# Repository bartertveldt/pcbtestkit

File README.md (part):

# PCB TestKit

**From a KiCad board to a production-test kit in one click: weak-point analysis, the fab class to order, a test
plan, a pogo-pin test fixture PCB, a 3D-printed solder jig, a Raspberry Pi test runner and an animated explainer
video. Built so AI assistants can drive it cheaply.**

*Rendered by KiCad itself from the KiCad demo board pic_programmer: the 55 hand-soldered parts are fitted with
the PCB top side up in the generated placement jig, the holding jig closes over them, the stack is turned over,
the placement jig comes off and every lead is soldered.*

---

## Contents

- [What you get](#what-you-get)
- [Install](#install)
- [Quick start](#quick-start)
- [Using it in KiCad](#using-it-in-kicad)
- [Command line](#command-line)
- [Technology classes: which fab and class to order](#technology-classes-which-fab-and-class-to-order)
- [The test fixture](#the-test-fixture)
- [The solder jigs](#the-solder-jigs)
- [The test runner (Raspberry Pi / MCU)](#the-test-runner-raspberry-pi--mcu)
- [Your own tester: test facilities](#your-own-tester-test-facilities)
- [Test environments: 100+ boards, one to three testers](#test-environments-100-boards-one-to-three-testers)
- [Visual guide and explainer video](#visual-guide-and-explainer-video)
- [AI assistants and automation](#ai-assistants-and-automation)
- [Configuration](#configuration-pcbtestkitjson)
- [Examples](#examples)
- [Validation](#validation)
- [Limitations](#limitations)
- [Security and privacy](#security-and-privacy)
- [Development](#development)
- [License](#license)

---

## What you get

| Output | What it is |
|---|---|
| **Weak-point analysis** | Production and life-cycle risks with locations: fab limits, acid traps, MLCCs near board edges, tombstoning, via-in-pad, THT pads on solid planes, electrolytics next to heat sources, SMD-only connectors, capacitor/resistor derating, decoupling, ESD, floating inputs, thermal pads, BOM gaps, schematic/board sync, testability. KiCad's own DRC/ERC are merged in when `kicad-cli` is available. |
| **Technology class** | Which class each fab's system needs (Eurocircuits `6C`, JLCPCB `standard`, OSH Park `4-layer`, ...), what drives it, whether the board fits at all, and every feature that breaks the class you order, with coordinates. |
| **`<board>-spec.json`** | A "good unit" specification: geometry, fab limits and measured stats, BOM with placement, connectivity, expected rail voltages, acceptance criteria, findings, decision log. |
| **`<board>-testplan.json`** | The test scheme: probe points, measurement channels, voltage dividers, header pinout and an ordered sequence (visual → short check → power-up/current → rails → signals → custom steps → power-off). |
| **`<board>-fixture.kicad_pcb`** | A bed-of-nails fixture PCB: pogo pins at the probe points, a header for the Pi/MCU, dividers, a power terminal, guide-pin holes from the board's mounting holes, cut-outs for tall parts and stacked boards, routed on two layers by the built-in router. One site per board for a batch, all on one connector in the middle; two plates (`-fixture-top` / `-fixture-bottom`) when probing both sides. |
| **`<board>-jig-placement.stl`, `<board>-jig.stl` / `.scad`** | Two 3D-printable solder jigs that work as a pair: fit the hand-soldered parts with the PCB top side up in the placement jig, close the holding jig over them, turn the stack over, lift off the placement jig and solder. Every part stays flush and square. Parts on both sides: a jig set per side (`-jig-bottom*.stl`) and a paste-print nest for the second SMD side. For a batch every jig holds several boards (as many as fit your printer bed). |
| **`runner/`** | A Raspberry Pi / microcontroller test runner that executes the plan board by board through a batch, programs each board through the fixture, with MicroPython firmware for RP2040/ESP32 front-ends. Testing with your own tester instead? Describe it as a [test facility](docs/FACILITIES.md): its fixed connector, plate, buses (CAN, USB, Ethernet, ...) and runner driver. |
| **`<board>-guide.html`** | Start here: a step-by-step visual guide with KiCad 3D renders and the explainer video. It covers what to fix, how to build the fixture, how to test and how to use the jigs. |
| **`<board>-report.html`** | Everything above on one page, with a board map. |
| **`<board>-explainer.mp4`** | Optional ~50 s video with real 3D animation rendered by KiCad: assembly, jig, fixture, test. |
| **`station.html`, `index.html`** | For a test station: every board type on it, with its videos. For a whole catalog: every board with its batch size, station and a short explanation, linked to its guide. See [The pages](#the-pages-one-board-a-station-a-catalog). |
| **AI interface** | 35 validated tools via CLI, MCP server and Python, an agent skill, `AGENTS.md` and `llms.txt`, designed for low token use. |

Everything runs locally. The core uses only the Python standard library and reads KiCad 6-10 files directly, so
it also works on the command line, in CI and on the Pi. No AI service or account is needed for any of it: every
decision (rail limits, which rails to test, part heights, accepted weak points, fixture or no fixture) can be made in
the KiCad dialog, and every file, including the jig STLs and the fixture board, is generated by the plugin itself,
identically on every run. An AI assistant is an optional extra that can make those judgement calls for you.

| Test fixture with the board above the pogo pins | Solder jig with the parts in place, PCB coming down |
|---|---|
|  |  |

---

## Install

### Requirements

| Need | For |
|---|---|
| KiCad 8, 9 or 10 | The plugin (toolbar button and dialog). KiCad 9+ for the 3D renders and the video. |
| Python 3.9+ | The CLI and MCP server outside KiCad (KiCad's own Python is used inside KiCad). No packages. |
| ffmpeg | Only for the explainer video. |

### Option 1: KiCad Plugin and Content Manager (recommended)

1. Download `pcbtestkit-<version>-kicad-pcm.zip` from the [latest release](https://github.com/bartertveldt/pcbtestkit/releases/latest).
2. In KiCad: **Plugin and Content Manager → Install from File...** and choose the zip.
3. In the PCB Editor: **Tools → External Plugins → Refresh Plugins** (or restart KiCad). The **PCB TestKit** button appears on the toolbar.

Once the package is in KiCad's official repository, it appears in the Plugin and Content Manager's list directly.

### Option 2: from a clone

```bash
git clone https://github.com/bartertveldt/pcbtestkit && cd pcbtestkit
python3 install.py                 # copies the plugin into every KiCad version folder it finds
python3 install.py --version 10.0  # one version only;  --uninstall removes it
```

`install.py` also installs the KiCad 9+/11 IPC-API variant (`plugin.json` + `ipc_main.py`), which keeps working
on KiCad 11 where the SWIG API is gone. Use `--no-ipc` on KiCad 9/10 if you only want the dialog version.

### Option 3: command line and MCP server only

```bash
pip install .            # in a clone (or pipx install .); gives the commands pcbtestkit and pcbtestkit-mcp
# or without installing anything:
python3 -m pcbtestkit --help      # from the repository folder
```

---

## Quick start

**In KiCad:** open the board, click **PCB TestKit**, press **Generate**. The summary and the HTML report open;
all files are in `<project>/production_test/`.

**On the command line:**

```bash
pcbtestkit analyze my_board.kicad_pcb            # weak points only (add --strict to fail CI on critical ones)
pcbtestkit classes check my_board.kicad_pcb      # which fab class systems the board fits
pcbtestkit run my_board.kicad_pcb                # everything, to <project>/production_test
pcbtestkit run my_board.kicad_pcb --video        # plus the 3D-animated explainer (several minutes)
```

**With an AI assistant:** give it this repository's skill or `AGENTS.md` (shell agents), or connect the MCP
server (chat apps). See [AI assistants and automation](#ai-assistants-and-automation).

---

## Using it in KiCad

1. Save the board, then click the toolbar button.
2. **Outputs:** output folder, fab profile, class system and class to order (it shows the class the board needs), extra checks such as IPC, and which files to generate (including the video).
3. **Test & fixture:** whether you want a fixture (generate a pogo-pin fixture board / I design my own, from a probe-point list / no fixture, manual test), probe side (auto, bottom, top or both), pogo family (P50/P75/P100) and mounting, signal policy, ADC range, supply voltage and current limits, fixture outline, boards per batch, routing, and the programming connector and command (it lists the programming headers it found).
4. **Rails:** the expected voltage and tolerance (or min/max range) of every power rail, and which rails to test. Rails whose voltage is not in the net name show a suggestion from the regulator part number.
5. **Stacked boards:** boards that sit on this one (daughter board, shield, display). Pin sockets and board-to-board connectors are listed as candidates; tick one and give its outline, height and whether it is fitted during the test.
6. **Solder jig:** tick the parts you hand-solder on either side (all THT parts by default), correct a part's height where its 3D model is generic, and choose the side order and the paste-print nest.
7. **Weak points:** check the board, then fix the listed problems in KiCad or tick the ones you accept, with a reason.
8. **AI assistant (optional):** ready-to-copy commands to connect an AI model to this project.
9. **Generate.**

Settings are stored in `pcbtestkit.json` next to the project. Commit it with the design.

---

## Command line

```bash
pcbtestkit run P [--out DIR] [--outline rect|outline] [--jig-parts J1,J2] [--no-visuals] [--video]
pcbtestkit run P --batch 4 --program-connector swd10    # 4 boards per fixture and jig set, ARM 10-pin SWD per board
pcbtestkit run P --class-system jlcpcb-2026 --tech-class standard --check-class ipc-2221-voltage:B2
pcbtestkit analyze P [--strict]                  # CI gate: exit 1 on critical findings
pcbtestkit init P                                # write a pcbtestkit.json template
pcbtestkit classes list | show <id> | check P [--system S --target C] | validate [file] | template | catalog
pcbtestkit facilities list | show <id> | validate [file] | template --out DIR    # your own tester
pcbtestkit run P --facility bench-tester-example                                  # fixture for that tester
pcbtestkit api <tool> --project P --args '<json>' --compact    # any agent tool, one JSON answer
pcbtestkit tools --brief | --name <tool> | --format mcp|anthropic|openai
pcbtestkit guide                                 # the agent quick reference
pcbtestkit mcp --project P [--profile core]      # MCP server
```

`P` is a `.kicad_pcb`, `.kicad_pro` or project folder. Exit codes: 0 ok, 1 findings/violations/tool error,
2 usage error. Every option: [docs/reference/cli.md](docs/reference/cli.md).

---

## Technology classes: which fab and class to order

Every fab describes "what we can build" differently, and the standards differently again. PCB TestKit checks all
of them with one engine; each **class system** is a small JSON file of data.

| System | Classes | Typical use |
|---|---|---|
| `eurocircuits-2024` (default) | pattern 3-9 × drill A-E, e.g. `6C` | EU pooling services |
| `jlcpcb-2026` | `standard`, `small-via` | JLCPCB (limits depend on layers, copper weight, finish) |
| `pcbway-standard-2026` | `standard`, `extra-charge-holes` | PCBWay standard PCB |
| `oshpark-2026` | `2-layer`, `2-layer-2oz-0.8mm`, `4-layer`, `6-layer` | OSH Park |
| `aisler-2025` | `2L-35um-HASL`, `2L-35um-ENIG`, `2L-70um-HASL`, `2L-70um-ENIG`, `4L-35um-ENIG`, `6L-35um-ENIG` | AISLER (all six stack-ups) |
| `wurth-basic-2022` | `standard`, `advanced` | Würth Elektronik BASIC rules |
| `seeed-fusion-2026` | `1oz`, `2oz`, `3oz` | Seeed Fusion standard FR4 (track/space per copper weight) |
| `nextpcb-2026` | `1oz`, `2oz` | NextPCB standard PCB (0.15 mm drill up to 1.2 mm thick) |
| `allpcb-2026` | `standard`, `aspect-8` | ALLPCB (aspect ratio 6:1, or 8:1 with an extra day) |
| `multicb-2026` | `standard`, `special` | Multi-CB (EU), 35 µm copper: free standard and special production |
| `ipc-2221-voltage` | `B2`, `B3`, `B4`, `A5` | Conductor spacing per voltage (set net voltages) |
| `ipc-6012-ring` | `1`, `2`, `3` | IPC-6012 annular ring and plating |

The board is measured once: every track; every different-net copper gap (exact pad shapes, per layer); every
ring, hole and hole-to-hole gap; hole to copper on every layer including plane clearances; copper and zone fills
to the board edge; mask webs, silkscreen, SMD pads; vias in pads, microvias and castellations; the smallest gap
per net pair, searched further for high-voltage nets. Each system then reports the class the board needs and what
drives it, whether it fits at all, violations of the class you order with locations, process limits, and order
notes for what a design can't show (e.g. IPC-6012 class 3 plating).

```bash
pcbtestkit classes check my_board.kicad_pcb
pcbtestkit classes check my_board.kicad_pcb --system jlcpcb-2026 --target standard   # exit 1 on violations (CI)
```

Set the class you order in the dialog, with `--class-system/--tech-class/--check-class`, in `pcbtestkit.json`
(`"tech": {"system": "jlcpcb-2026", "class": "standard", "context": {"finish": "ENIG"}}`) or through the AI tools.
The ordered class also sets the limits of the generic manufacturing checks.

**Adding a fab or standard takes no code:** `pcbtestkit classes template`, type the numbers as the source writes
them (`"4mil"`, `"100um"`), add test vectors, `pcbtestkit classes validate`, and drop the file in
`~/.pcbtestkit/classsystems/` or `<project>/classsystems/`. [docs/CLASS_SYSTEMS.md](docs/CLASS_SYSTEMS.md) covers
the framework, the source and check date of every built-in number, and the roadmap.

---

## The test fixture

`fixture.mode` (the **Test fixture** choice in the dialog) picks one of three:

| Mode | You get |
|---|---|
| `generate` (default) | the pogo-pin fixture board described below |
| `own` | `<board>-probe-points.csv`: every probe point with KiCad coordinates, net, role, probe side, suggested tip, test channel and expected voltage, so you can design the fixture yourself; the runner bundle is still written |
| `none` | no fixture and no runner: the guide lists the test points and limits for a manual test with a bench supply and a multimeter |

For `generate`:

- Open `<board>-fixture.kicad_pcb` in KiCad: pogo pins, header, dividers and holes are placed and **routed** by the built-in
  router (two layers, 0.25 mm signal and 0.5 mm GND/VIN tracks, KiCad's default clearances, vias where needed). Each
  divider pair sits above its own header pin. Run DRC and order it. A connection the router cannot make is listed in
  the warnings and stays as ratsnest for you to route; `--no-route` (or `"route": false`) leaves the whole board unrouted.
  Track and via sizes: `fixture.track_mm`, `power_track_mm`, `clearance_mm`, `via_mm`, `via_drill_mm`.
- **Probe side.** `auto` plans both sides and picks the better one (rails reached first, dedicated test pads preferred, component solder joints avoided). `bottom`: the board lies on the fixture as is. `top`: mirrored for a board placed face down. `both`: two fixture plates with the board between them (a clamshell); each net is probed on whichever side has the best target, each plate gets its own header, and channel numbers are shared. A plate that would carry no probe is not made. When `auto` leaves rails that only the other side reaches, the report and the open decisions suggest `both`.
- **Pogo drills** are typical values for receptacle-mounted pins (P50 0.9 mm, P75 1.4 mm, P100 1.7 mm) or direct-solder pins; check your pin's datasheet and set `testplan.pogo_drill_mm` if needed. Probe spacing is the larger of the family pitch and pad diameter + 0.5 mm. Tips: `crown` for THT leads, `spear` for flat pads.
- **Nest and clamp per board** (default): see below. With `fixture.nest.enabled: false`, **guide pins** go through
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
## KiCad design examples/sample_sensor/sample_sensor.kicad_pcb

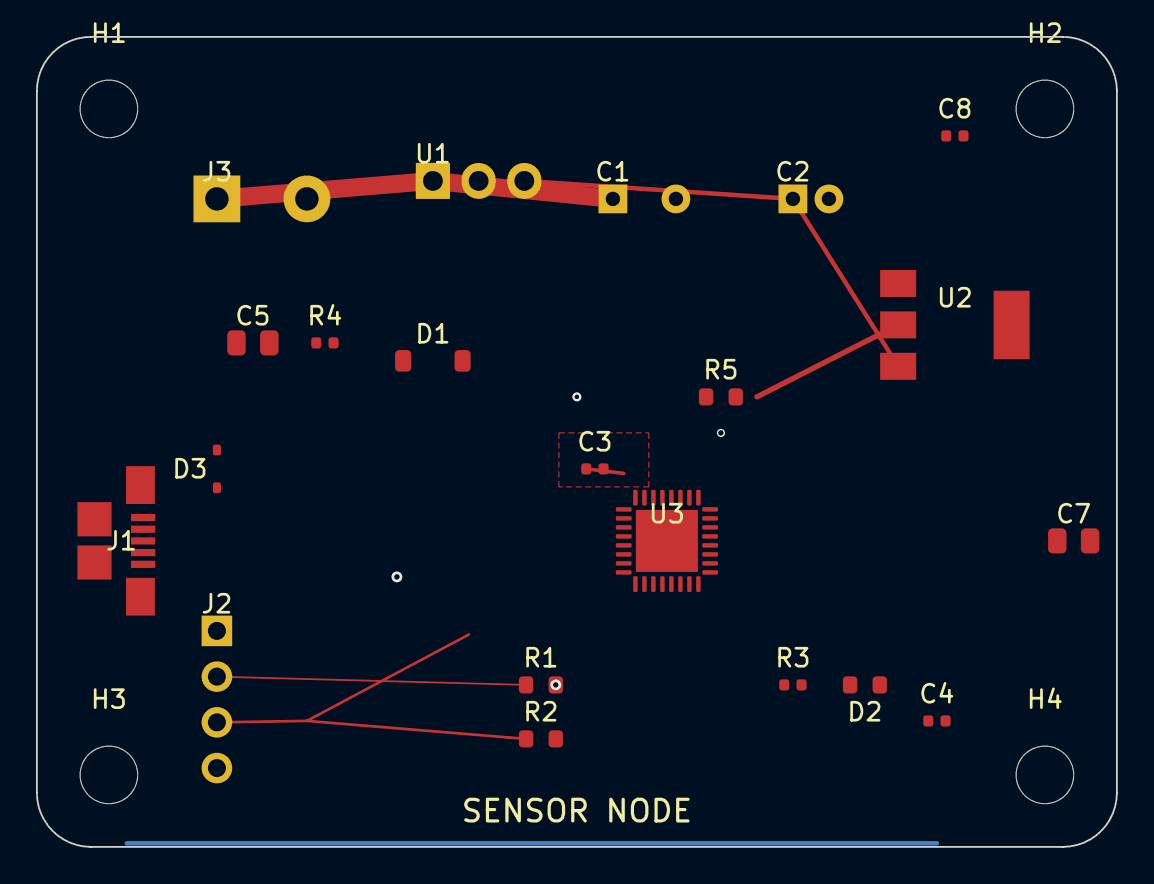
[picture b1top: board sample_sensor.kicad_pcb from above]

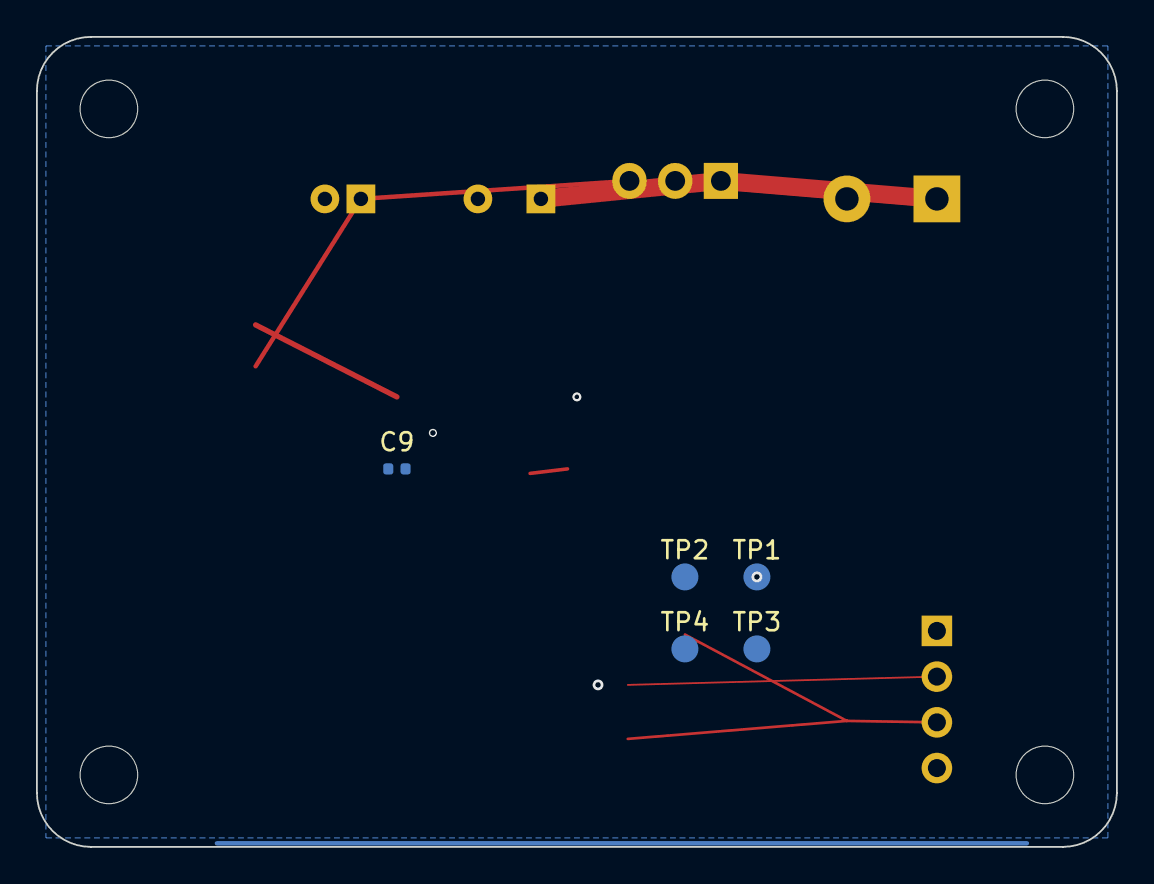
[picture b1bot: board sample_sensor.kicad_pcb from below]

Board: 2 copper layers, 60.0 x 45.0 mm, 30 parts (5 on the bottom side), 12 nets.

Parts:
C1: 100uF 25V; CP_Radial_D8.0mm_P3.50mm
C2: 47uF 6.3V; CP_Radial_D5.0mm_P2.00mm
C3, C4, C8, C9: 100nF; C_0402_1005Metric
C5: 1uF 16V; C_0805_2012Metric
C7: 10uF 10V; C_0805_2012Metric
D1: SS14; D_SOD-123
D2: GREEN; LED_0603_1608Metric
D3: PESD5V0S1BL; D_SOD-323
H1, H2, H3, H4: MountingHole; MountingHole_3.2mm_M3
J1: USB_B_Micro; USB_Micro-B_Molex-105017-0001
J2: I2C; PinHeader_1x04_P2.54mm_Vertical
J3: 12V IN; TerminalBlock_Phoenix_MKDS-1,5-2_1x02_P5.00mm_Horizontal
R1, R2: 4k7; R_0603_1608Metric
R3: 330; R_0402_1005Metric
R4: 1k; R_0402_1005Metric
R5: 10k; R_0603_1608Metric
TP1: +3V3; TestPoint_Pad_D1.5mm
TP2: +5V; TestPoint_Pad_D1.5mm
TP3: GND; TestPoint_Pad_D1.5mm
TP4: SDA; TestPoint_Pad_D1.5mm
U1: LM7805_TO220; TO-220-3_Vertical
U2: AMS1117-3.3; SOT-223-3_TabPin2
U3: STM32G031K8U6; QFN-32-1EP_5x5mm_P0.5mm_EP3.45x3.45mm

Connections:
+3V3: C3.1, C4.1, C7.1, C8.1, C9.1, J2.1, R1.2, R2.2, R5.2, TP1.1, U2.2 (VO), U2.4 (VO), U3.1 (VDD), U3.24 (VDD)
+5V: C2.1, D1.1 (K), TP2.1, U1.3 (OUT), U2.3 (VI)
/D+: J1.3, U3.22 (PA12)
/D-: J1.2, U3.21 (PA11)
/LED: R3.1, U3.20 (PA5)
/NRST: R5.1, U3.2 (NRST)
/SCL: J2.3, R2.1, U3.10 (PB6)
/SDA: J2.2, R1.1, TP4.1, U3.9 (PB7)
GND: C1.2, C2.2, C3.2, C4.2, C5.2, C7.2, C8.2, C9.2, D2.1, D3.2 (A), J1.5, J1.6, J2.4, J3.2, R4.2, TP3.1, U1.2 (GND), U2.1 (GND), U3.16 (VSS), U3.32 (VSS), U3.33 (EP)
unnamed: D2.2, R3.2
VBUS: D1.2 (A), D3.1 (K), J1.1
VIN_12V: C1.1, C5.1, J3.1, R4.1, U1.1 (IN)

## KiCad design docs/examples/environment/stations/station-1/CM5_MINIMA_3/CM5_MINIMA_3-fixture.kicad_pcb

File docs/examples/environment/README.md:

# A test environment for 128 boards

Made with `pcbtestkit environment build` for 110 boards generated by `examples/make_collection.py` (seed 7), then KiCad's demo projects added with `pcbtestkit environment add` (the station video shows the demos after the boards it showed first). Start with [index.html](index.html), [requirements.md](requirements.md), [constraints.md](constraints.md) (what limits every board) and [upgrades.md](upgrades.md) (what an upgrade would gain and cost).

Everything at the environment and station level is here: the overview video, the stations' KiCad boards, pages and videos, the ranking and every board's profile. Every board's own outputs (guide, report, fixture, nest and clamp parts, jigs, runner) come to about 3 GB, so the repository keeps 5 boards, each with its explainer video:

* [sensor_20](stations/station-1/sensor_20/sensor_20-guide.html)
* [usb_dongle_09](stations/station-1/usb_dongle_09/usb_dongle_09-guide.html)
* [CM5 MINIMA](stations/station-1/CM5_MINIMA_3/CM5_MINIMA_3-guide.html)
* [Antmicro Baseboard for Jetson AGX Thor](stations/station-1/jetson-agx-thor-baseboard/jetson-agx-thor-baseboard-guide.html)
* [KiCad demo](stations/station-2/video/video-guide.html)

[.gitignore](.gitignore) lists them; `python3 tools/regen_examples.py --only environment` makes the catalog again and keeps the boards it lists.

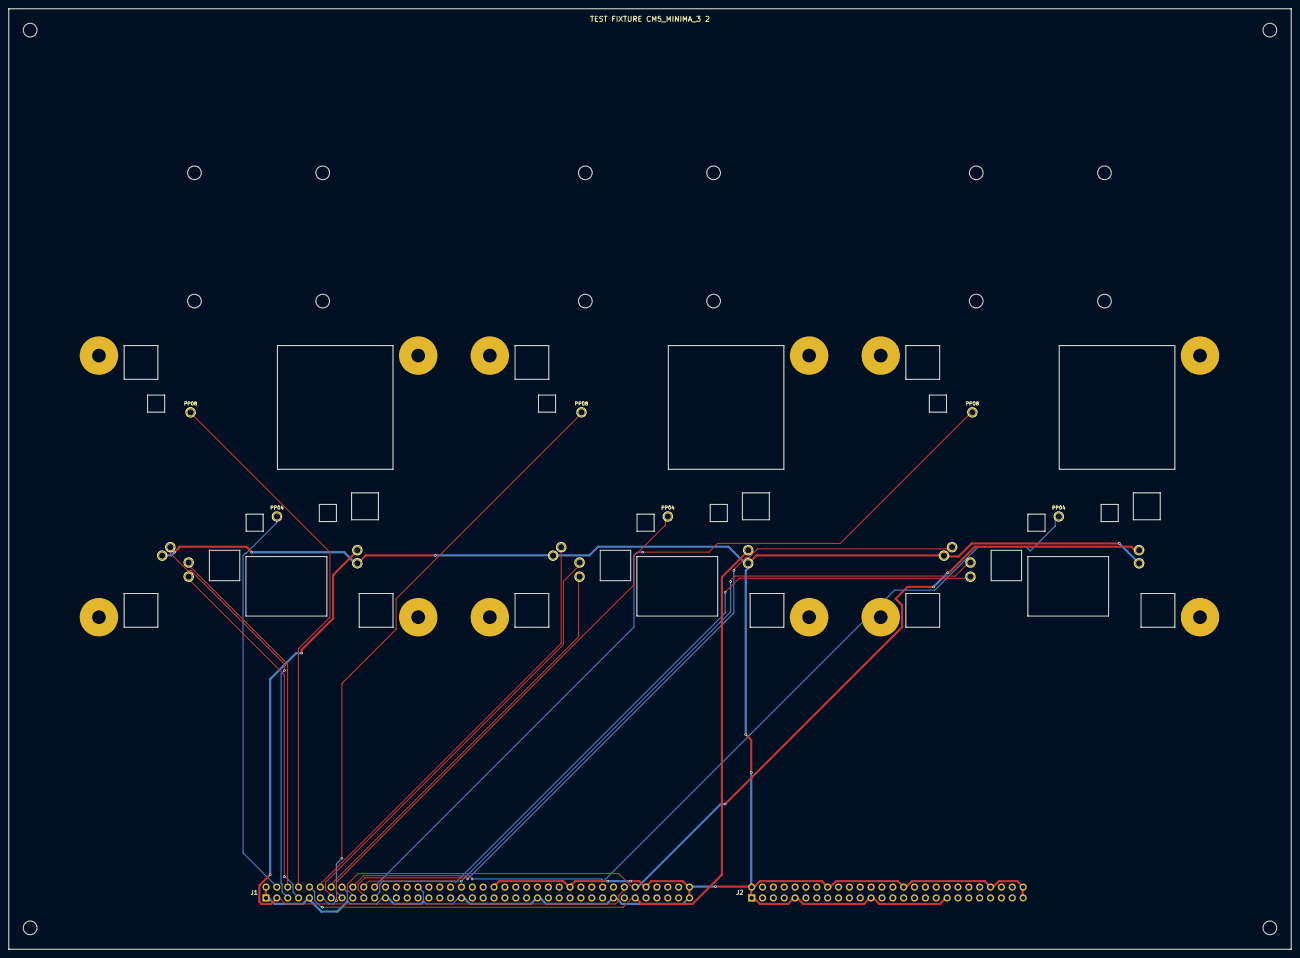
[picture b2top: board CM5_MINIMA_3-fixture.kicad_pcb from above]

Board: 2 copper layers, 300.0 x 220.0 mm, 60 parts (0 on the bottom side), 19 nets.

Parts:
H1, H2, H3, H4: M3; MountingHole_3.2mm
J1: J1; PinHeader_2x40_P2.54mm_Vertical
J2: J2; PinHeader_2x26_P2.54mm_Vertical
K1, K2, K3: TOGGLE CLAMP; ToggleClamp
N1, N2, N3: NEST; Nest
NK1, NK2, NK3, NK4, NK5, NK6, NK7, NK8, NK9, NK10, NK11, NK12: CLAMP M3; ClampScrew_M3
NP1, NP2, NP3, NP4, NP5, NP6, NP7, NP8, NP9, NP10, NP11, NP12: STANDOFF M3; NestPost_M3
P1, P9, P17: VBUS_USB2.0; Pogo_P75_receptacle
P2, P3, P10, P11, P18, P19: GND; Pogo_P75_receptacle
P4, P12, P20: +3V3_PI; Pogo_P75_receptacle
P5, P13, P21: +5V; Pogo_P75_receptacle
P6, P14, P22: M2_3V3; Pogo_P75_receptacle
P7, P15, P23: M2_LX; Pogo_P75_receptacle
P8, P16, P24: Net-(J701-SUSCLK); Pogo_P75_receptacle

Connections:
GND: J1.1 (GND), J1.2 (GND), J1.9 (GND), J1.16 (GND), J1.23 (GND), J1.30 (GND), J1.37 (GND), J1.44 (GND), J1.51 (GND), J1.58 (GND), J1.65 (GND), J1.72 (GND), J1.79 (GND), J1.80 (GND), J2.1 (GND), J2.2 (GND), J2.9 (GND), J2.16 (GND), J2.23 (GND), J2.30 (GND), J2.37 (GND), J2.46 (GND), J2.51 (GND), J2.52 (GND), P2.1, P3.1, P10.1, P11.1, P18.1, P19.1
S1_TP_+3V3_PI: J1.4 (AIN2), P4.1
S1_TP_+5V: J1.5 (AIN3), P5.1
S1_TP_M2_3V3: J1.6 (AIN4), P6.1
S1_TP_M2_LX: J1.7 (AIN5), P7.1
S1_TP_Net-_J701-SUSCLK: J1.8 (AIN6), P8.1
S1_VIN: J1.3 (AIN1), J1.68 (VOUT1), P1.1
S2_TP_+3V3_PI: J1.11 (AIN8), P12.1
S2_TP_+5V: J1.12 (AIN9), P13.1
S2_TP_M2_3V3: J1.13 (AIN10), P14.1
S2_TP_M2_LX: J1.14 (AIN11), P15.1
S2_TP_Net-_J701-SUSCLK: J1.15 (AIN12), P16.1
S2_VIN: J1.10 (AIN7), J1.69 (VOUT2), P9.1
S3_TP_+3V3_PI: J1.18 (AIN14), P20.1
S3_TP_+5V: J1.19 (AIN15), P21.1
S3_TP_M2_3V3: J1.20 (AIN16), P22.1
S3_TP_M2_LX: J1.21 (AIN17), P23.1
S3_TP_Net-_J701-SUSCLK: J1.22 (AIN18), P24.1
S3_VIN: J1.17 (AIN13), J1.70 (VOUT3), P17.1

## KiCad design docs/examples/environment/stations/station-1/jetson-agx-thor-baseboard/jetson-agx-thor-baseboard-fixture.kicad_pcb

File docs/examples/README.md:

# Example outputs

Complete PCB TestKit exports for four boards, one test station and one test environment, generated with `tools/regen_examples.py`, which runs:

```bash
python3 -m pcbtestkit run <board>.kicad_pcb --video
```

| Folder | Board | Why it is interesting |
|---|---|---|
| `sample_sensor/` | The bundled sample (60 × 45 mm, 2 layers) | It has seeded weak points. Its 0.45/0.30 mm vias leave a 0.025 mm ring on the drill tool, which is finer than any Eurocircuits pool class. The report shows what to widen and which other fabs accept the board as drawn. The probes use the bottom test pads, and the jig holds 5 THT parts, cut to their 3D shapes; the TO-220 regulator, its ground tab on the ground pour, gets room for a heat-resistant insert. `jig-fit-check/` has the board and its jigs in their working position, in KiCad's 3D coordinates. The fixture is routed (26 connections, 11 vias). |
| `pic_programmer/` | KiCad demo *pic_programmer* (2 layers, through-hole) | It needs only Eurocircuits class 3A. The jig holds 56 hand-soldered parts (the D-sub J1 now too). The fixture is routed (51 connections, 31 vias). |
| `tiny_tapeout/` | KiCad demo *tiny_tapeout* (Tiny Tapeout demo board: RP2040, 104 × 81 mm, 4 layers) | **The showcase.** A batch of four boards: one fixture with four sites around one connector in the middle, jigs that hold two boards each (two sets for the printer bed), and a runner that programs all four RP2040s over SWD at the same time (`program.command` with a probe per board) while it measures the rails, then the checks that need the firmware. The guide has the production timing (timeline per board, time per board by batch size). The video shows every step, ending with the batch on the fixture and the tested copper lighting up next to the runner's output. Settings: `SHOWCASE` in `tools/regen_examples.py`. |
| `station/` | The example test station (`examples/make_station.py`: 260 × 190 mm, a 2 × 40 socket with 32 analog inputs, 4 supplies, 2 CAN, 2 UART, 4 I2C) with four board types: the sample and the KiCad demos *stickhub*, *royalblue54L_feather* and *pic_programmer* | **Swapping products on one tester.** `station.html` shows how many boards of each type one fixture takes and what limits it (supplies, UART buses, the plate), every type's pin map on the station's connector and how to swap fixtures. Every fixture has the station's outline, holes and the mating connector in the same place; every board in it has its own nest and toggle clamp. `station-compatibility.mp4` slides each fixture onto the station with its boards; each board type's folder has its own guide, outputs and video. Made with `pcbtestkit station run`. |
| `environment/` | A test environment for 128 boards: 110 generated by `examples/make_collection.py` (sensor nodes, CAN nodes, RS-485 I/O, USB dongles, gateways with Ethernet, power boards, large controllers, AVR boards, and some that cannot fit by design) and KiCad's demo projects | **One tester for a whole product range.** `index.html` shows the stations designed for the collection, exactly what each one needs (`requirements.md`: analog inputs, supplies with their voltages, every bus with the boards that use it, programmers per interface, plate, sockets), the ranking of all 128 boards with their batch sizes and what limits them, and every board that does not fit with the reason. Each station has its KiCad board, page and swap video; `test-environment.mp4` joins them. Five boards are complete, each with its explainer video (guide, report, fixture, nest and clamp parts, jigs, runner): the best-ranked board with a batch of ten, a batch of eight programmed over SWD, the Raspberry Pi CM5 carrier, the 1,123-part Jetson baseboard and the one board on station-2. Every board's outputs together are about 3 GB, so `environment/.gitignore` lists the boards the repository keeps; `tools/regen_examples.py --only environment` makes the whole catalog and keeps those. |
| `video/` | KiCad demo *video* (312 mm PCI card, 4 layers) | It needs Eurocircuits class 4B. The class overview shows that its zone fills come within 0.011 mm of the edge, which JLCPCB, OSH Park and Würth flag. The fixture has 32 measurement channels, each divider pair above its own header pin, and is routed (134 connections, 121 vias). Its four BNC connectors get room for heat-resistant inserts in the holding jig. |

## How to use the outputs

Each folder holds:

* **`<board>-guide.html`** — start here. It's the step-by-step visual guide, readable on a phone or tablet at the workstation:
  1. What to fix before ordering, the technology class to order, and which fabs' class systems the board fits.
  2. Building the fixture: parts list, build steps, and wiring from the header to the ADS1115 boards and the Raspberry Pi.
  3. Running a test.
  4. Hand-soldering with the two jigs: the six steps with a KiCad render under each (both jigs printed, the parts going into the placement jig, the holding jig coming down, the stack turned over, soldering), the placement jig and the pocket map.
* **`<board>-explainer.mp4`** — the same story as a short video for operators, with 3D animation rendered by KiCad: assembly, printing both jigs, fitting the parts in the placement jig, closing the holding jig, turning the stack over, soldering, building the fixture, and pressing the board onto the pins.
* **`<board>-fixture.kicad_pcb`** (+ `.kicad_pro`) — open it in KiCad, run DRC and order it (since 1.1.0 it comes out routed; route anything the warnings list). The pogo pins, every board's nest and its clamp have 3D models, so press Alt+3 to see them.
* **`<board>-fixture-nest.stl`**, **`-fixture-press-plate.stl`** and **`-fixture-clamp-adapter.stl`** — every board's nest (it slides in on the rails, above the pogo pins), the press plate for the toggle clamp's spindle and the clamp's adapter: print one of each per board. The guide's fixture section has the parts list, the heights and the assembly steps.
* **`<board>-jig-placement.stl`** and **`<board>-jig.stl`** — the two solder jigs; print them as they are. Fit the parts with the PCB top side up in the placement jig, put the holding jig on top, turn the stack over, lift off the placement jig and solder. The holding jig also comes as `.scad` for OpenSCAD.
* **`runner/`** — copy it to the Raspberry Pi. `testplan.json` is already inside; describe your wiring in `hardware.json`.
* **`<board>-spec.json`, `<board>-testplan.json`, `<board>-report.html`** — the machine-readable specification and test plan, and the full findings report.
* **`visuals/`** — the KiCad 3D renders used in the guide.

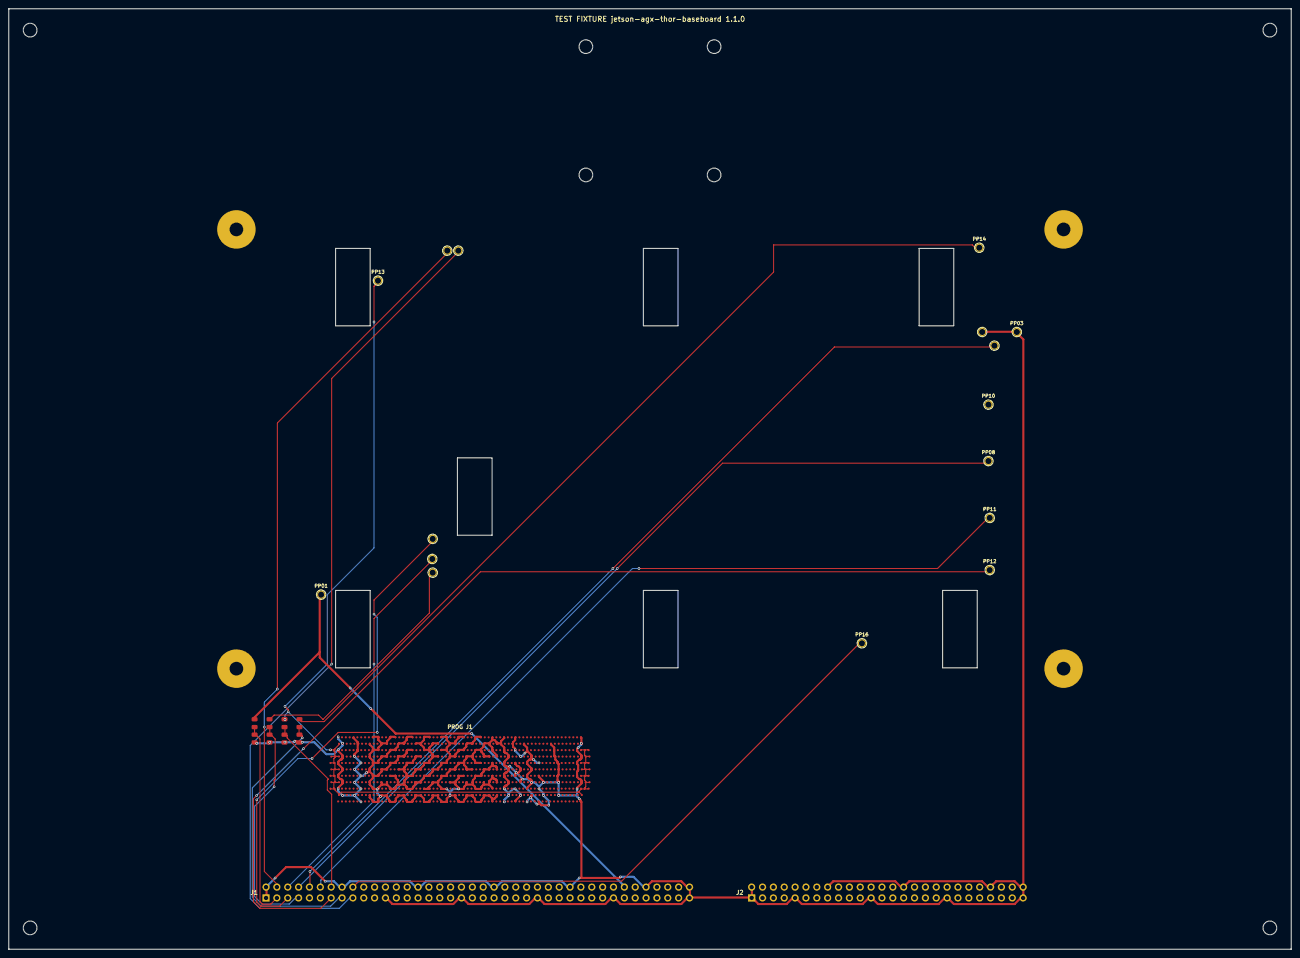
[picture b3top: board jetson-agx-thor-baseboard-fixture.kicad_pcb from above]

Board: 2 copper layers, 300.0 x 220.0 mm, 41 parts (0 on the bottom side), 19 nets.

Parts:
H1, H2, H3, H4: M3; MountingHole_3.2mm
J1: J1; PinHeader_2x40_P2.54mm_Vertical
J2: J2; PinHeader_2x26_P2.54mm_Vertical
K1: TOGGLE CLAMP; ToggleClamp
N1: NEST; Nest
NK1, NK2, NK3, NK4: CLAMP M3; ClampScrew_M3
NP1, NP2, NP3, NP4: STANDOFF M3; NestPost_M3
P1: +12V_FMC; Pogo_P75_receptacle
P2, P3: GND; Pogo_P75_receptacle
P4: +3V3; Pogo_P75_receptacle
P5: +3V3_FMC; Pogo_P75_receptacle
P6: +5V_FMC; Pogo_P75_receptacle
P7: +VCC_FMC; Pogo_P75_receptacle
P8: USBC2_VBUS; Pogo_P75_receptacle
P9: USBC0_VBUS; Pogo_P75_receptacle
P10: USBC1_VBUS; Pogo_P75_receptacle
P11: USBC3_VBUS; Pogo_P75_receptacle
P12: USBC4_VBUS; Pogo_P75_receptacle
P13: SYS_VIN_HV; Pogo_P75_receptacle
P14: VCC_IN; Pogo_P75_receptacle
P15: SFI_CLK+; Pogo_P75_receptacle
P16: SH; Pogo_P75_receptacle
PRG1: PROG J1; Conn_Hermaphroditic_Molex_203456-0003_mirrored
R1: 4.3k; R_0805_2012Metric
R2, R4, R6, R8: 10k; R_0805_2012Metric
R3, R5, R7: 15k; R_0805_2012Metric

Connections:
CH01: J1.3 (AIN1), R1.1, R2.2
CH05: J1.7 (AIN5), R3.1, R4.2
CH11: J1.14 (AIN11), R5.1, R6.2
CH12: J1.15 (AIN12), R7.1, R8.2
GND: J1.1 (GND), J1.2 (GND), J1.9 (GND), J1.16 (GND), J1.23 (GND), J1.30 (GND), J1.37 (GND), J1.44 (GND), J1.51 (GND), J1.58 (GND), J1.65 (GND), J1.72 (GND), J1.79 (GND), J1.80 (GND), J2.1 (GND), J2.2 (GND), J2.9 (GND), J2.16 (GND), J2.23 (GND), J2.30 (GND), J2.37 (GND), J2.46 (GND), J2.51 (GND), J2.52 (GND), P2.1, P3.1, PRG1.A9 (GND), PRG1.A12 (GND), PRG1.A13 (GND), PRG1.A16 (GND), PRG1.A17 (GND), PRG1.A20 (GND), PRG1.A21 (GND), PRG1.A24 (GND), PRG1.A25 (GND), PRG1.A28 (GND), PRG1.A29 (GND), PRG1.A32 (GND), PRG1.A33 (GND), PRG1.A36 (GND), PRG1.A37 (GND), PRG1.A40 (GND), PRG1.A43 (GND), PRG1.A46 (GND), PRG1.A49 (GND), PRG1.A52 (GND), PRG1.A63 (GND), PRG1.B4 (GND), PRG1.B7 (GND), PRG1.B11 (GND), PRG1.B14 (GND), PRG1.B15 (GND), PRG1.B18 (GND), PRG1.B19 (GND), PRG1.B22 (GND), PRG1.B23 (GND), PRG1.B26 (GND), PRG1.B27 (GND), PRG1.B30 (GND), PRG1.B31 (GND), PRG1.B34 (GND), PRG1.B35 (GND), PRG1.B38 (GND), PRG1.B39 (GND), PRG1.B41 (GND), PRG1.B44 (GND), PRG1.B47 (GND), PRG1.B50 (GND), PRG1.B53 (GND), PRG1.B57 (GND), PRG1.C3 (GND), PRG1.C9 (GND), PRG1.C12 (GND), PRG1.C13 (GND), PRG1.C16 (GND), PRG1.C17 (GND), PRG1.C20 (GND), PRG1.C21 (GND), PRG1.C24 (GND), PRG1.C25 (GND), PRG1.C28 (GND), PRG1.C29 (GND), PRG1.C32 (GND), PRG1.C33 (GND), PRG1.C36 (GND), PRG1.C37 (GND), PRG1.C40 (GND), PRG1.C43 (GND), PRG1.C46 (GND), PRG1.C49 (GND), PRG1.C52 (GND), PRG1.C62 (GND), PRG1.D4 (GND), PRG1.D7 (GND), PRG1.D11 (GND), PRG1.D14 (GND), PRG1.D15 (GND), PRG1.D18 (GND), PRG1.D19 (GND), PRG1.D22 (GND), PRG1.D23 (GND), PRG1.D26 (GND), PRG1.D27 (GND), PRG1.D30 (GND), PRG1.D31 (GND), PRG1.D34 (GND), PRG1.D35 (GND), PRG1.D38 (GND), PRG1.D39 (GND), PRG1.D41 (GND), PRG1.D44 (GND), PRG1.D47 (GND), PRG1.D50 (GND), PRG1.D53 (GND), PRG1.D57 (GND), PRG1.D63 (GND), PRG1.E3 (GND), PRG1.E9 (GND), PRG1.E12 (GND), PRG1.E13 (GND), PRG1.E16 (GND), PRG1.E17 (GND), PRG1.E20 (GND), PRG1.E21 (GND), PRG1.E24 (GND), PRG1.E25 (GND), PRG1.E28 (GND), PRG1.E29 (GND), PRG1.E32 (GND), PRG1.E33 (GND), PRG1.E36 (GND), PRG1.E37 (GND), PRG1.E40 (GND), PRG1.E43 (GND), PRG1.E46 (GND), PRG1.E49 (GND), PRG1.E52 (GND), PRG1.E57 (GND), PRG1.E62 (GND), PRG1.F4 (GND), PRG1.F7 (GND), PRG1.F11 (GND), PRG1.F14 (GND), PRG1.F15 (GND), PRG1.F18 (GND), PRG1.F19 (GND), PRG1.F22 (GND), PRG1.F23 (GND), PRG1.F26 (GND), PRG1.F27 (GND), PRG1.F30 (GND), PRG1.F31 (GND), PRG1.F34 (GND), PRG1.F35 (GND), PRG1.F38 (GND), PRG1.F39 (GND), PRG1.F41 (GND), PRG1.F44 (GND), PRG1.F47 (GND), PRG1.F50 (GND), PRG1.F57 (GND), PRG1.F62 (GND), PRG1.G3 (GND), PRG1.G9 (GND), PRG1.G12 (GND), PRG1.G13 (GND), PRG1.G16 (GND), PRG1.G17 (GND), PRG1.G20 (GND), PRG1.G21 (GND), PRG1.G24 (GND), PRG1.G25 (GND), PRG1.G28 (GND), PRG1.G29 (GND), PRG1.G32 (GND), PRG1.G33 (GND), PRG1.G36 (GND), PRG1.G37 (GND), PRG1.G40 (GND), PRG1.G43 (GND), PRG1.G46 (GND), PRG1.G49 (GND), PRG1.G52 (GND), PRG1.G57 (GND), PRG1.G62 (GND), PRG1.H4 (GND), PRG1.H7 (GND), PRG1.H11 (GND), PRG1.H14 (GND), PRG1.H15 (GND), PRG1.H18 (GND), PRG1.H19 (GND), PRG1.H22 (GND), PRG1.H23 (GND), PRG1.H26 (GND), PRG1.H27 (GND), PRG1.H30 (GND), PRG1.H31 (GND), PRG1.H34 (GND), PRG1.H35 (GND), PRG1.H38 (GND), PRG1.H39 (GND), PRG1.H41 (GND), PRG1.H44 (GND), PRG1.H47 (GND), PRG1.H50 (GND), PRG1.H56 (GND), PRG1.H63 (GND), PRG1.J3 (GND), PRG1.J8 (GND), PRG1.J12 (GND), PRG1.J13 (GND), PRG1.J16 (GND), PRG1.J17 (GND), PRG1.J20 (GND), PRG1.J21 (GND), PRG1.J24 (GND), PRG1.J25 (GND), PRG1.J28 (GND), PRG1.J29 (GND), PRG1.J32 (GND), PRG1.J33 (GND), PRG1.J36 (GND), PRG1.J37 (GND), PRG1.J40 (GND), PRG1.J43 (GND), PRG1.J46 (GND), PRG1.J49 (GND), PRG1.J56 (GND), PRG1.J62 (GND), PRG1.K4 (GND), PRG1.K8 (GND), PRG1.K11 (GND), PRG1.K14 (GND), PRG1.K15 (GND), PRG1.K18 (GND), PRG1.K19 (GND), PRG1.K22 (GND), PRG1.K23 (GND), PRG1.K26 (GND), PRG1.K27 (GND), PRG1.K30 (GND), PRG1.K31 (GND), PRG1.K34 (GND), PRG1.K35 (GND), PRG1.K38 (GND), PRG1.K39 (GND), PRG1.K41 (GND), PRG1.K42 (GND), PRG1.K45 (GND), PRG1.K48 (GND), PRG1.K55 (GND), PRG1.K63 (GND), PRG1.L3 (GND), PRG1.L7 (GND), PRG1.L12 (GND), PRG1.L13 (GND), PRG1.L16 (GND), PRG1.L17 (GND), PRG1.L20 (GND), PRG1.L21 (GND), PRG1.L24 (GND), PRG1.L25 (GND), PRG1.L28 (GND), PRG1.L29 (GND), PRG1.L32 (GND), PRG1.L33 (GND), PRG1.L36 (GND), PRG1.L37 (GND), PRG1.L40 (GND), PRG1.L43 (GND), PRG1.L46 (GND), PRG1.L63 (GND), R2.1, R4.1, R6.1, R8.1
TP_+3V3: J1.4 (AIN2), P4.1
TP_+3V3_FMC: J1.5 (AIN3), P5.1
TP_+5V_FMC: J1.6 (AIN4), P6.1
TP_+VCC_FMC: P7.1, R3.2
TP_SFI_CLK+: J1.17 (AIN13), P15.1
TP_SH: J1.18 (AIN14), P16.1
TP_SYS_VIN_HV: P13.1, PRG1.B3 (VREF), PRG1.B63 (VREF), PRG1.C1 (VREF), PRG1.C2 (VREF), PRG1.C63 (VREF), PRG1.C64 (VREF), PRG1.C65 (VREF), PRG1.D1 (VREF), PRG1.D2 (VREF), PRG1.D3 (VREF), PRG1.D64 (VREF), PRG1.D65 (VREF), PRG1.E1 (VREF), PRG1.E2 (VREF), PRG1.E63 (VREF), PRG1.E64 (VREF), PRG1.E65 (VREF), PRG1.F1 (VREF), PRG1.F2 (VREF), PRG1.F3 (VREF), PRG1.F63 (VREF), PRG1.F64 (VREF), PRG1.F65 (VREF), PRG1.G1 (VREF), PRG1.G2 (VREF), PRG1.G63 (VREF), PRG1.G64 (VREF), PRG1.G65 (VREF), PRG1.H1 (VREF), PRG1.H2 (VREF), PRG1.H3 (VREF), PRG1.H64 (VREF), PRG1.H65 (VREF), PRG1.J1 (VREF), PRG1.J2 (VREF), PRG1.J63 (VREF), PRG1.J64 (VREF), PRG1.J65 (VREF), PRG1.K3 (VREF), R5.2
TP_USBC0_VBUS: J1.10 (AIN7), P9.1
TP_USBC1_VBUS: J1.11 (AIN8), P10.1
TP_USBC2_VBUS: J1.8 (AIN6), P8.1
TP_USBC3_VBUS: J1.12 (AIN9), P11.1
TP_USBC4_VBUS: J1.13 (AIN10), P12.1
TP_VCC_IN: P14.1, R7.2
VIN: J1.68 (VOUT1), P1.1, R1.2

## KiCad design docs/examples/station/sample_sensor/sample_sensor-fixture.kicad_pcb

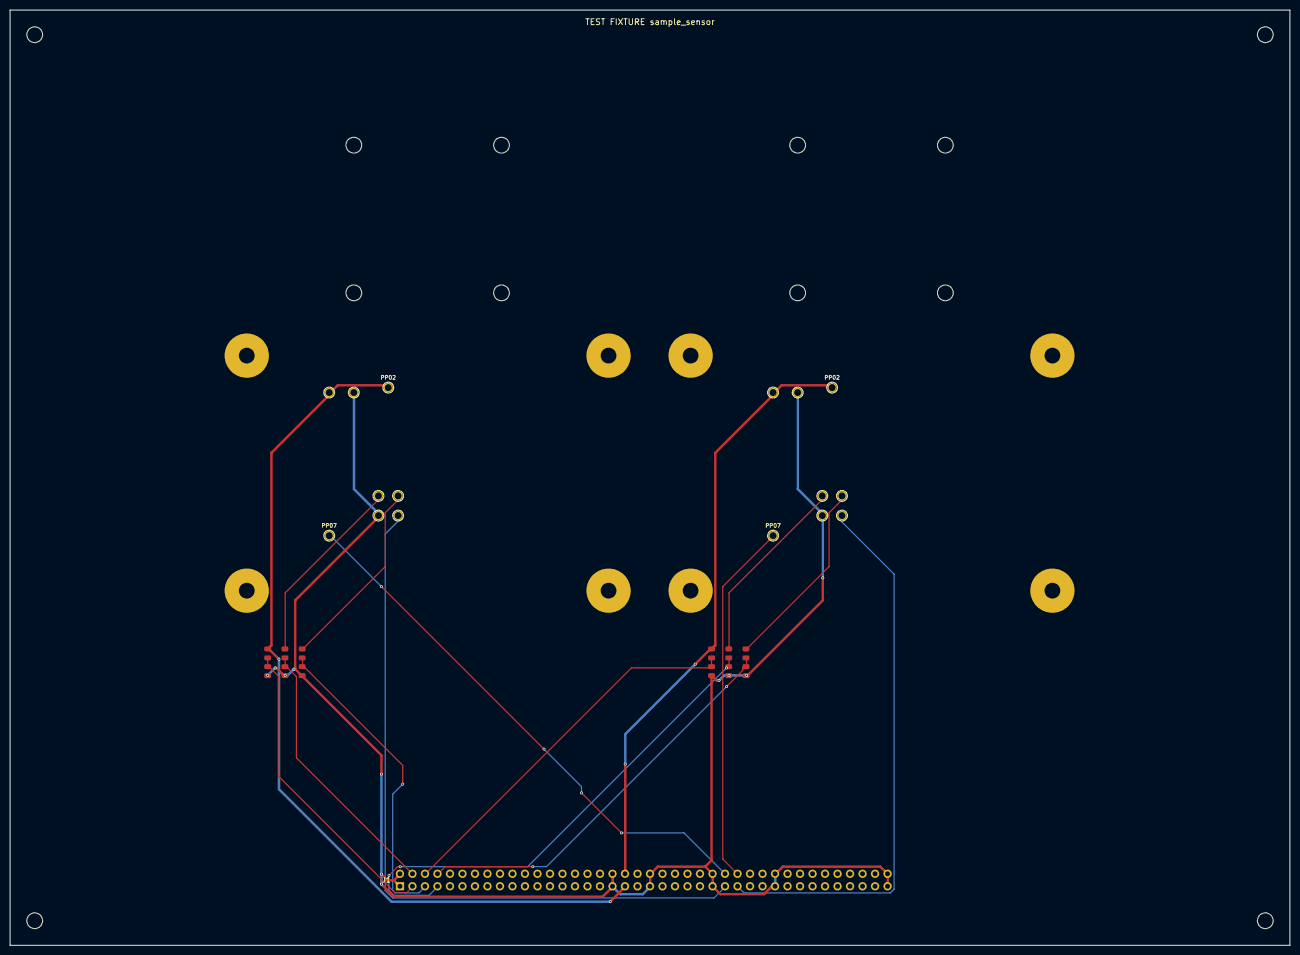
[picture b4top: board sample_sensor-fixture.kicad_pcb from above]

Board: 2 copper layers, 260.0 x 190.0 mm, 53 parts (0 on the bottom side), 17 nets.

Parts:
H1, H2, H3, H4: M3; MountingHole_3.2mm
J1: J1; PinHeader_2x40_P2.54mm_Vertical
K1, K2: TOGGLE CLAMP; ToggleClamp
N1, N2: NEST; Nest
NK1, NK2, NK3, NK4, NK5, NK6, NK7, NK8: CLAMP M3; ClampScrew_M3
NP1, NP2, NP3, NP4, NP5, NP6, NP7, NP8: STANDOFF M3; NestPost_M3
P1, P2, P9, P10: VIN_12V; Pogo_P75_receptacle
P3, P4, P11, P12: GND; Pogo_P75_receptacle
P5, P13: +3V3; Pogo_P75_receptacle
P6, P14: +5V; Pogo_P75_receptacle
P7, P15: SCL; Pogo_P75_receptacle
P8, P16: SDA; Pogo_P75_receptacle
R1, R7: 33k; R_0805_2012Metric
R2, R4, R6, R8, R10, R12: 10k; R_0805_2012Metric
R3, R9: 1.8k; R_0805_2012Metric
R5, R11: 8.2k; R_0805_2012Metric

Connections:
GND: J1.1 (GND), J1.2 (GND), J1.35 (GND), J1.36 (GND), J1.41 (GND), J1.42 (GND), J1.51 (GND), J1.52 (GND), J1.61 (GND), J1.62 (GND), J1.79 (GND), J1.80 (GND), P3.1, P4.1, P11.1, P12.1, R2.1, R4.1, R6.1, R8.1, R10.1, R12.1
S1_CH01: J1.3 (AIN1), R1.1, R2.2
S1_CH02: J1.4 (AIN2), R3.1, R4.2
S1_CH03: J1.5 (AIN3), R5.1, R6.2
S1_TP_+3V3: P5.1, R3.2
S1_TP_+5V: P6.1, R5.2
S1_TP_SCL: J1.54 (I2C_SCL), P7.1
S1_TP_SDA: J1.53 (I2C_SDA), P8.1
S1_VIN: J1.37 (VOUT1), P1.1, P2.1, R1.2
S2_CH01: J1.6 (AIN4), R7.1, R8.2
S2_CH02: J1.7 (AIN5), R9.1, R10.2
S2_CH03: J1.8 (AIN6), R11.1, R12.2
S2_TP_+3V3: P13.1, R9.2
S2_TP_+5V: P14.1, R11.2
S2_TP_SCL: J1.56 (I2C2_SCL), P15.1
S2_TP_SDA: J1.55 (I2C2_SDA), P16.1
S2_VIN: J1.38 (VOUT2), P9.1, P10.1, R7.2

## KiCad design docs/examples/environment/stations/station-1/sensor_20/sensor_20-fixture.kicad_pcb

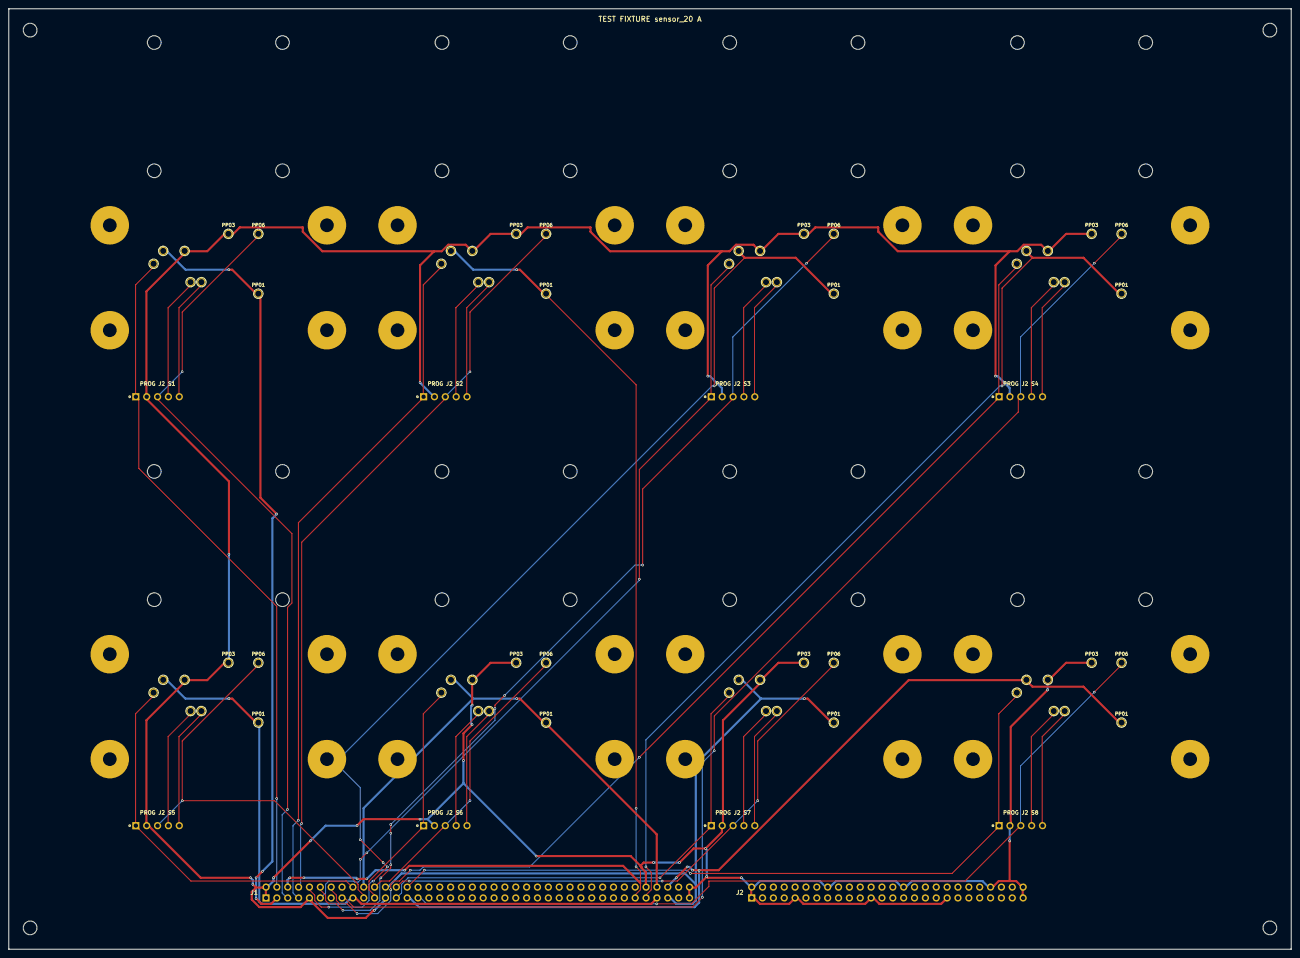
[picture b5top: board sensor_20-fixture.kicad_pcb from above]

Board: 2 copper layers, 300.0 x 220.0 mm, 158 parts (0 on the bottom side), 41 nets.

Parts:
H1, H2, H3, H4: M3; MountingHole_3.2mm
J1: J1; PinHeader_2x40_P2.54mm_Vertical
J2: J2; PinHeader_2x26_P2.54mm_Vertical
K1, K2, K3, K4, K5, K6, K7, K8: TOGGLE CLAMP; ToggleClamp
N1, N2, N3, N4, N5, N6, N7, N8: NEST; Nest
NK1, NK2, NK3, NK4, NK5, NK6, NK7, NK8, NK9, NK10, NK11, NK12, NK13, NK14, NK15, NK16, NK17, NK18, NK19, NK20, NK21, NK22, NK23, NK24, NK25, NK26, NK27, NK28, NK29, NK30, NK31, NK32: CLAMP M3; ClampScrew_M3
NP1, NP2, NP3, NP4, NP5, NP6, NP7, NP8, NP9, NP10, NP11, NP12, NP13, NP14, NP15, NP16, NP17, NP18, NP19, NP20, NP21, NP22, NP23, NP24, NP25, NP26, NP27, NP28, NP29, NP30, NP31, NP32: STANDOFF M3; NestPost_M3
P1, P2, P9, P10, P17, P18, P25, P26, P33, P34, P41, P42, P49, P50, P57, P58: VIN_5V; Pogo_P75_receptacle
P3, P4, P11, P12, P19, P20, P27, P28, P35, P36, P43, P44, P51, P52, P59, P60: GND; Pogo_P75_receptacle
P5, P13, P21, P29, P37, P45, P53, P61: +3V3; Pogo_P75_receptacle
P6, P14, P22, P30, P38, P46, P54, P62: SWDIO; Pogo_P75_receptacle
P7, P15, P23, P31, P39, P47, P55, P63: SWCLK; Pogo_P75_receptacle
P8, P16, P24, P32, P40, P48, P56, P64: NRST; Pogo_P75_receptacle
PRG1: PROG J2 S1; PinHeader_1x05_P2.54mm_Vertical
PRG2: PROG J2 S2; PinHeader_1x05_P2.54mm_Vertical
PRG3: PROG J2 S3; PinHeader_1x05_P2.54mm_Vertical
PRG4: PROG J2 S4; PinHeader_1x05_P2.54mm_Vertical
PRG5: PROG J2 S5; PinHeader_1x05_P2.54mm_Vertical
PRG6: PROG J2 S6; PinHeader_1x05_P2.54mm_Vertical
PRG7: PROG J2 S7; PinHeader_1x05_P2.54mm_Vertical
PRG8: PROG J2 S8; PinHeader_1x05_P2.54mm_Vertical

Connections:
GND: J1.1 (GND), J1.2 (GND), J1.9 (GND), J1.16 (GND), J1.23 (GND), J1.30 (GND), J1.37 (GND), J1.44 (GND), J1.51 (GND), J1.58 (GND), J1.65 (GND), J1.72 (GND), J1.79 (GND), J1.80 (GND), J2.1 (GND), J2.2 (GND), J2.9 (GND), J2.16 (GND), J2.23 (GND), J2.30 (GND), J2.37 (GND), J2.46 (GND), J2.51 (GND), J2.52 (GND), P3.1, P4.1, P11.1, P12.1, P19.1, P20.1, P27.1, P28.1, P35.1, P36.1, P43.1, P44.1, P51.1, P52.1, P59.1, P60.1, PRG1.2 (GND), PRG2.2 (GND), PRG3.2 (GND), PRG4.2 (GND), PRG5.2 (GND), PRG6.2 (GND), PRG7.2 (GND), PRG8.2 (GND)
S1_TP_+3V3: J1.4 (AIN2), P5.1, PRG1.1 (VREF)
S1_TP_NRST: P8.1, PRG1.5 (NRST)
S1_TP_SWCLK: P7.1, PRG1.4 (SWCLK)
S1_TP_SWDIO: J1.5 (AIN3), P6.1, PRG1.3 (SWDIO)
S1_VIN: J1.3 (AIN1), J1.68 (VOUT1), P1.1, P2.1
S2_TP_+3V3: J1.7 (AIN5), P13.1, PRG2.1 (VREF)
S2_TP_NRST: P16.1, PRG2.5 (NRST)
S2_TP_SWCLK: P15.1, PRG2.4 (SWCLK)
S2_TP_SWDIO: J1.8 (AIN6), P14.1, PRG2.3 (SWDIO)
S2_VIN: J1.6 (AIN4), J1.69 (VOUT2), P9.1, P10.1
S3_TP_+3V3: J1.11 (AIN8), P21.1, PRG3.1 (VREF)
S3_TP_NRST: P24.1, PRG3.5 (NRST)
S3_TP_SWCLK: P23.1, PRG3.4 (SWCLK)
S3_TP_SWDIO: J1.12 (AIN9), P22.1, PRG3.3 (SWDIO)
S3_VIN: J1.10 (AIN7), J1.70 (VOUT3), P17.1, P18.1
S4_TP_+3V3: J1.14 (AIN11), P29.1, PRG4.1 (VREF)
S4_TP_NRST: P32.1, PRG4.5 (NRST)
S4_TP_SWCLK: P31.1, PRG4.4 (SWCLK)
S4_TP_SWDIO: J1.15 (AIN12), P30.1, PRG4.3 (SWDIO)
S4_VIN: J1.13 (AIN10), J1.71 (VOUT4), P25.1, P26.1
S5_TP_+3V3: J1.18 (AIN14), P37.1, PRG5.1 (VREF)
S5_TP_NRST: P40.1, PRG5.5 (NRST)
S5_TP_SWCLK: P39.1, PRG5.4 (SWCLK)
S5_TP_SWDIO: J1.19 (AIN15), P38.1, PRG5.3 (SWDIO)
S5_VIN: J1.17 (AIN13), J1.73 (VOUT5), P33.1, P34.1
S6_TP_+3V3: J1.21 (AIN17), P45.1, PRG6.1 (VREF)
S6_TP_NRST: P48.1, PRG6.5 (NRST)
S6_TP_SWCLK: P47.1, PRG6.4 (SWCLK)
S6_TP_SWDIO: J1.22 (AIN18), P46.1, PRG6.3 (SWDIO)
S6_VIN: J1.20 (AIN16), J1.74 (VOUT6), P41.1, P42.1
S7_TP_+3V3: J1.25 (AIN20), P53.1, PRG7.1 (VREF)
S7_TP_NRST: P56.1, PRG7.5 (NRST)
S7_TP_SWCLK: P55.1, PRG7.4 (SWCLK)
S7_TP_SWDIO: J1.26 (AIN21), P54.1, PRG7.3 (SWDIO)
S7_VIN: J1.24 (AIN19), J1.75 (VOUT7), P49.1, P50.1
S8_TP_+3V3: J1.28 (AIN23), P61.1, PRG8.1 (VREF)
S8_TP_NRST: P64.1, PRG8.5 (NRST)
S8_TP_SWCLK: P63.1, PRG8.4 (SWCLK)
S8_TP_SWDIO: J1.29 (AIN24), P62.1, PRG8.3 (SWDIO)
S8_VIN: J1.27 (AIN22), J1.76 (VOUT8), P57.1, P58.1

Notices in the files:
README.md:
License:
[MIT](LICENSE) © 2026 Bart Ertveldt.
Most example outputs in `docs/examples/` were made from demo projects that ship with KiCad. They keep the licence of
the board they were made from and credit its authors: see [docs/examples/LICENSES.md](docs/examples/LICENSES.md).
The board designs themselves are not in this repository.
License: MIT
